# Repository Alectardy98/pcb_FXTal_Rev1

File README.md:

# FXTal Rev. 1 
    A Drop In Replacement PCB For The IBM Model F XT

All Supported Layouts can be seen [HERE](http://www.keyboard-layout-editor.com/#/gists/daab9567d1fe4691fd52719a6adab8b0)

xwhatsit/QMK atmega32u4 pcb for the IBM Model F XT and IBM Bigfoot

This version has been tested and has shown to function properly in both supported layouts.
- The firmware can be found in the firmware folder
- All files for production though JLCPCB can be found in the JLCPCB folder
- This pcb requires an xwhatsit to function, see [purdeaandrei's open source files](https://github.com/purdeaandrei/SMDModelFController)
- Test Points are currently on the pcb, when building make sure to cover the bottom test points with eletrical tape to prevent a short
- The origonal backplate will need to be modified to remove the right PCB mounting peg, to prevent interfearance
- The barrel Plate will need to be modified, a scan of the required holes are provided in folder meta, to help with the task

The PCB thickness should be 0.6mm or 0.08mm. This is thin enough to allow the board to flex into shape.
- 0.8mm tested and working

Standard glossy soldermask is probably the best choice. JLCPCB has had issues with wear on their black soldermask before. They have changed the formula, but a standard green/red/blue/yellow/purple/white/etc. glossy solder mask is probaby the safest bet for keyswitch wear resistance. Higher wear resistance might also be achieved by coating the front of the capacitive pads in silkscreen, as silkscreen is an extra layer of epoxy. I am unsure how this will affect keyfeel or actuation, however.

For connecting the board to an xwhatsit or other controller, I would recommend [3M 8132/06 100](https://www.digikey.com/en/products/detail/3m/8132-06-100/7809902), which has the correct pitch to connect this pcb to an xwhatsit

Capacitive pad footprints have been taken dvjs project the mtf-capacitive Other mesurements have been taken by NeonKight and myself from an origonal IBM F XT. The key matrix of the PCB is custom, made by myself guided by dvjs and purdeaandrei.

Released without warranty, use at your own risk.  
PRs & feedback welcome!

| Authors | 

Alectardy98

| Special Thanks |

djvs - for generial and overall help.   
NeonKnight - for mesurments and reversenginering.   
purdeaandrei - for writing the QMK firmware to work with xwhatsit.

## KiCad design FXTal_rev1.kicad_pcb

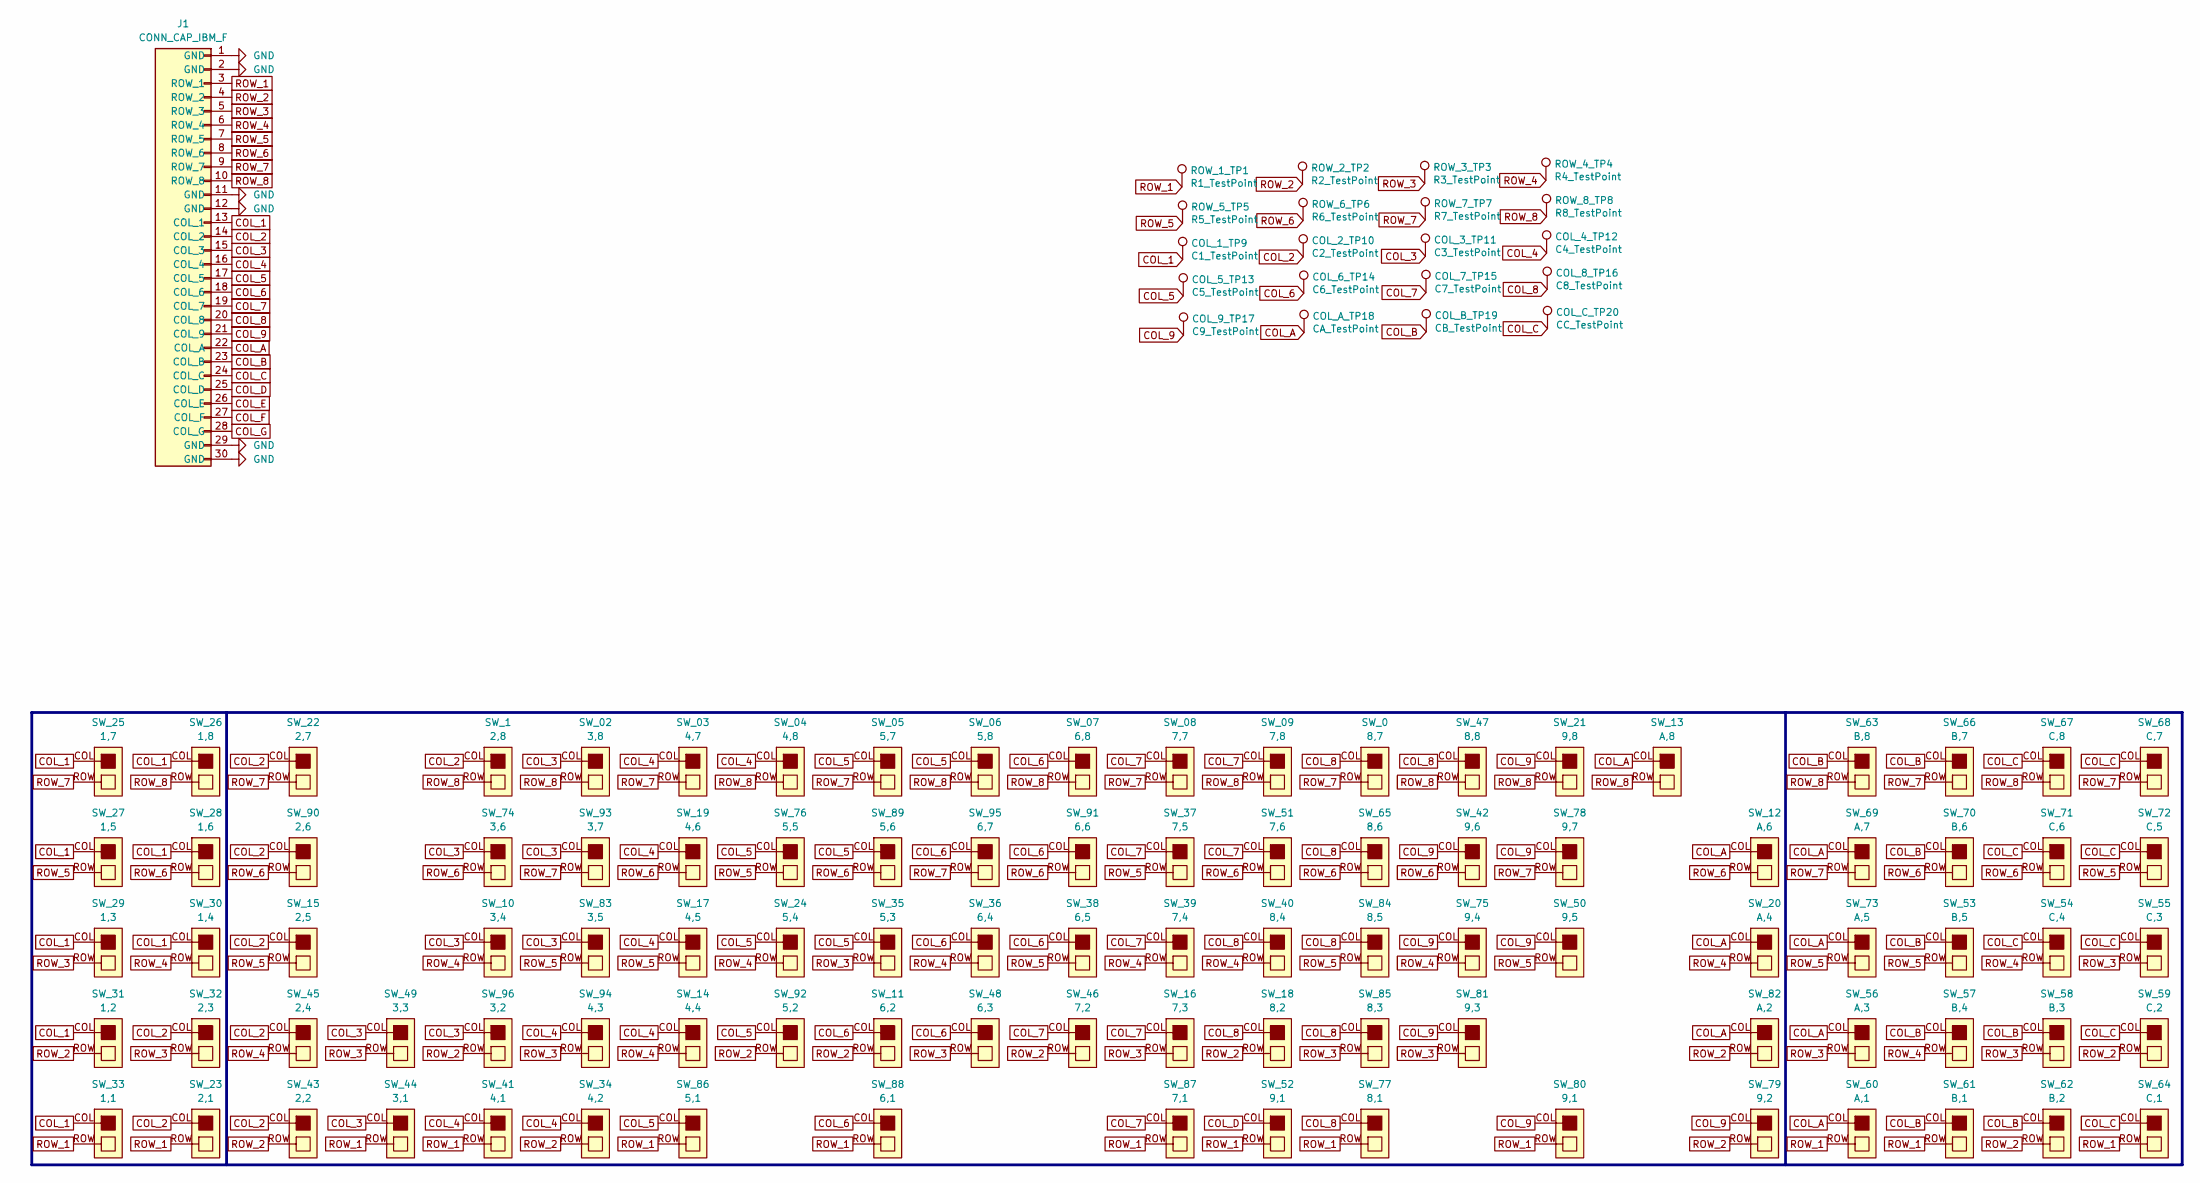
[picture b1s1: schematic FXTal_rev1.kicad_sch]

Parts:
COL_1_TP9: C1_TestPoint; TestPoint_Pad_D1.0mm
COL_2_TP10: C2_TestPoint; TestPoint_Pad_D1.0mm
COL_3_TP11: C3_TestPoint; TestPoint_Pad_D1.0mm
COL_4_TP12: C4_TestPoint; TestPoint_Pad_D1.0mm
COL_5_TP13: C5_TestPoint; TestPoint_Pad_D1.0mm
COL_6_TP14: C6_TestPoint; TestPoint_Pad_D1.0mm
COL_7_TP15: C7_TestPoint; TestPoint_Pad_D1.0mm
COL_8_TP16: C8_TestPoint; TestPoint_Pad_D1.0mm
COL_9_TP17: C9_TestPoint; TestPoint_Pad_D1.0mm
COL_A_TP18: CA_TestPoint; TestPoint_Pad_D1.0mm
COL_B_TP19: CB_TestPoint; TestPoint_Pad_D1.0mm
COL_C_TP20: CC_TestPoint; TestPoint_Pad_D1.0mm
J1: CONN_CAP_IBM_F
ROW_1_TP1: R1_TestPoint; TestPoint_Pad_D1.0mm
ROW_2_TP2: R2_TestPoint; TestPoint_Pad_D1.0mm
ROW_3_TP3: R3_TestPoint; TestPoint_Pad_D1.0mm
ROW_4_TP4: R4_TestPoint; TestPoint_Pad_D1.0mm
ROW_5_TP5: R5_TestPoint; TestPoint_Pad_D1.0mm
ROW_6_TP6: R6_TestPoint; TestPoint_Pad_D1.0mm
ROW_7_TP7: R7_TestPoint; TestPoint_Pad_D1.0mm
ROW_8_TP8: R8_TestPoint; TestPoint_Pad_D1.0mm
SW_0: 8,7; SW_CAP_IBM_F_ALT
SW_1: 2,8; SW_CAP_IBM_F
SW_02: 3,8; SW_CAP_IBM_F_ALT
SW_03: 4,7; SW_CAP_IBM_F
SW_04: 4,8; SW_CAP_IBM_F_ALT
SW_05: 5,7; SW_CAP_IBM_F
SW_06: 5,8; SW_CAP_IBM_F_ALT
SW_07: 6,8; SW_CAP_IBM_F
SW_08: 7,7; SW_CAP_IBM_F_ALT
SW_09: 7,8; SW_CAP_IBM_F
SW_10: 3,4; SW_CAP_IBM_F
SW_11: 6,2; SW_CAP_IBM_F
SW_12: A,6; SW_CAP_IBM_F_ALT
SW_13: A,8; SW_CAP_IBM_F
SW_14: 4,4; SW_CAP_IBM_F_ALT
SW_15: 2,5; SW_CAP_IBM_F
SW_16: 7,3; SW_CAP_IBM_F_ALT
SW_17: 4,5; SW_CAP_IBM_F
SW_18: 8,2; SW_CAP_IBM_F
SW_19: 4,6; SW_CAP_IBM_F
SW_20: A,4; SW_CAP_IBM_F
SW_21: 9,8; SW_CAP_IBM_F_ALT
SW_22: 2,7; SW_CAP_IBM_F_ALT
SW_23: 2,1; SW_CAP_IBM_F
SW_24: 5,4; SW_CAP_IBM_F_ALT
SW_25: 1,7; SW_CAP_IBM_F_ALT
SW_26: 1,8; SW_CAP_IBM_F
SW_27: 1,5; SW_CAP_IBM_F_ALT
SW_28: 1,6; SW_CAP_IBM_F
SW_29: 1,3; SW_CAP_IBM_F_ALT
SW_30: 1,4; SW_CAP_IBM_F
SW_31: 1,2; SW_CAP_IBM_F_ALT
SW_32: 2,3; SW_CAP_IBM_F
SW_33: 1,1; SW_CAP_IBM_F_ALT
SW_34: 4,2; SW_CAP_IBM_F
SW_35: 5,3; SW_CAP_IBM_F
SW_36: 6,4; SW_CAP_IBM_F_ALT
SW_37: 7,5; SW_CAP_IBM_F
SW_38: 6,5; SW_CAP_IBM_F
SW_39: 7,4; SW_CAP_IBM_F_ALT
SW_40: 8,4; SW_CAP_IBM_F
SW_41: 4,1; SW_CAP_IBM_F_ALT
SW_42: 9,6; SW_CAP_IBM_F
SW_43: 2,2; SW_CAP_IBM_F
SW_44: 3,1; SW_CAP_IBM_F_ALT
SW_45: 2,4; SW_CAP_IBM_F
SW_46: 7,2; SW_CAP_IBM_F_ALT
SW_47: 8,8; SW_CAP_IBM_F
SW_48: 6,3; SW_CAP_IBM_F_ALT
SW_49: 3,3; SW_CAP_IBM_F_ALT
SW_50: 9,5; SW_CAP_IBM_F_ALT
SW_51: 7,6; SW_CAP_IBM_F_ALT
SW_52: 9,1; CAL_CAP_IBM_F
SW_53: B,5; SW_CAP_IBM_F
SW_54: C,4; SW_CAP_IBM_F_ALT
SW_55: C,3; SW_CAP_IBM_F
SW_56: A,3; SW_CAP_IBM_F_ALT
SW_57: B,4; SW_CAP_IBM_F
SW_58: B,3; SW_CAP_IBM_F
SW_59: C,2; SW_CAP_IBM_F_ALT
SW_60: A,1; SW_CAP_IBM_F_ALT
SW_61: B,1; SW_CAP_IBM_F
SW_62: B,2; SW_CAP_IBM_F_ALT
SW_63: B,8; SW_CAP_IBM_F
SW_64: C,1; SW_CAP_IBM_F
SW_65: 8,6; SW_CAP_IBM_F
SW_66: B,7; SW_CAP_IBM_F_ALT
SW_67: C,8; SW_CAP_IBM_F
SW_68: C,7; SW_CAP_IBM_F_ALT
SW_69: A,7; SW_CAP_IBM_F_ALT
SW_70: B,6; SW_CAP_IBM_F
SW_71: C,6; SW_CAP_IBM_F
SW_72: C,5; SW_CAP_IBM_F_ALT
SW_73: A,5; SW_CAP_IBM_F_ALT
SW_74: 3,6; SW_CAP_IBM_F_ALT
SW_75: 9,4; SW_CAP_IBM_F
SW_76: 5,5; SW_CAP_IBM_F
SW_77: 8,1; SW_CAP_IBM_F_ALT
SW_78: 9,7; SW_CAP_IBM_F
SW_79: 9,2; SW_CAP_IBM_F_ALT
SW_80: 9,1; SW_CAP_IBM_F_ALT
SW_81: 9,3; SW_CAP_IBM_F
SW_82: A,2; SW_CAP_IBM_F
SW_83: 3,5; SW_CAP_IBM_F_ALT
SW_84: 8,5; SW_CAP_IBM_F_ALT
SW_85: 8,3; SW_CAP_IBM_F_ALT
SW_86: 5,1; SW_CAP_IBM_F
SW_87: 7,1; SW_CAP_IBM_F_ALT
SW_88: 6,1; SW_CAP_IBM_F_ALT
SW_89: 5,6; SW_CAP_IBM_F_ALT
SW_90: 2,6; SW_CAP_IBM_F_ALT
SW_91: 6,6; SW_CAP_IBM_F
SW_92: 5,2; SW_CAP_IBM_F_ALT
SW_93: 3,7; SW_CAP_IBM_F_ALT
SW_94: 4,3; SW_CAP_IBM_F
SW_95: 6,7; SW_CAP_IBM_F_ALT
SW_96: 3,2; SW_CAP_IBM_F

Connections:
COL_1: COL_1_TP9.1, J1.13 (COL_1), SW_25.COL, SW_26.COL, SW_27.COL, SW_28.COL, SW_29.COL, SW_30.COL, SW_31.COL, SW_33.COL
COL_2: COL_2_TP10.1, J1.14 (COL_2), SW_1.COL, SW_15.COL, SW_22.COL, SW_23.COL, SW_32.COL, SW_43.COL, SW_45.COL, SW_90.COL
COL_3: COL_3_TP11.1, J1.15 (COL_3), SW_02.COL, SW_10.COL, SW_44.COL, SW_49.COL, SW_74.COL, SW_83.COL, SW_93.COL, SW_96.COL
COL_4: COL_4_TP12.1, J1.16 (COL_4), SW_03.COL, SW_04.COL, SW_14.COL, SW_17.COL, SW_19.COL, SW_34.COL, SW_41.COL, SW_94.COL
COL_5: COL_5_TP13.1, J1.17 (COL_5), SW_05.COL, SW_06.COL, SW_24.COL, SW_35.COL, SW_76.COL, SW_86.COL, SW_89.COL, SW_92.COL
COL_6: COL_6_TP14.1, J1.18 (COL_6), SW_07.COL, SW_11.COL, SW_36.COL, SW_38.COL, SW_48.COL, SW_88.COL, SW_91.COL, SW_95.COL
COL_7: COL_7_TP15.1, J1.19 (COL_7), SW_08.COL, SW_09.COL, SW_16.COL, SW_37.COL, SW_39.COL, SW_46.COL, SW_51.COL, SW_87.COL
COL_8: COL_8_TP16.1, J1.20 (COL_8), SW_0.COL, SW_18.COL, SW_40.COL, SW_47.COL, SW_65.COL, SW_77.COL, SW_84.COL, SW_85.COL
COL_9: COL_9_TP17.1, J1.21 (COL_9), SW_21.COL, SW_42.COL, SW_50.COL, SW_75.COL, SW_78.COL, SW_79.COL, SW_80.COL, SW_81.COL
COL_A: COL_A_TP18.1, J1.22 (COL_A), SW_12.COL, SW_13.COL, SW_20.COL, SW_56.COL, SW_60.COL, SW_69.COL, SW_73.COL, SW_82.COL
COL_B: COL_B_TP19.1, J1.23 (COL_B), SW_53.COL, SW_57.COL, SW_58.COL, SW_61.COL, SW_62.COL, SW_63.COL, SW_66.COL, SW_70.COL
COL_C: COL_C_TP20.1, J1.24 (COL_C), SW_54.COL, SW_55.COL, SW_59.COL, SW_64.COL, SW_67.COL, SW_68.COL, SW_71.COL, SW_72.COL
COL_D: J1.25 (COL_D), SW_52.COL
COL_E: J1.26 (COL_E)
COL_F: J1.27 (COL_F)
COL_G: J1.28 (COL_G)
GND: J1.1 (GND), J1.2 (GND), J1.11 (GND), J1.12 (GND), J1.29 (GND), J1.30 (GND)
ROW_1: J1.3 (ROW_1), ROW_1_TP1.1, SW_23.ROW, SW_33.ROW, SW_41.ROW, SW_44.ROW, SW_52.ROW, SW_60.ROW, SW_61.ROW, SW_64.ROW, SW_77.ROW, SW_80.ROW, SW_86.ROW, SW_87.ROW, SW_88.ROW
ROW_2: J1.4 (ROW_2), ROW_2_TP2.1, SW_11.ROW, SW_18.ROW, SW_31.ROW, SW_34.ROW, SW_43.ROW, SW_46.ROW, SW_59.ROW, SW_62.ROW, SW_79.ROW, SW_82.ROW, SW_92.ROW, SW_96.ROW
ROW_3: J1.5 (ROW_3), ROW_3_TP3.1, SW_16.ROW, SW_29.ROW, SW_32.ROW, SW_35.ROW, SW_48.ROW, SW_49.ROW, SW_55.ROW, SW_56.ROW, SW_58.ROW, SW_81.ROW, SW_85.ROW, SW_94.ROW
ROW_4: J1.6 (ROW_4), ROW_4_TP4.1, SW_10.ROW, SW_14.ROW, SW_20.ROW, SW_24.ROW, SW_30.ROW, SW_36.ROW, SW_39.ROW, SW_40.ROW, SW_45.ROW, SW_54.ROW, SW_57.ROW, SW_75.ROW
ROW_5: J1.7 (ROW_5), ROW_5_TP5.1, SW_15.ROW, SW_17.ROW, SW_27.ROW, SW_37.ROW, SW_38.ROW, SW_50.ROW, SW_53.ROW, SW_72.ROW, SW_73.ROW, SW_76.ROW, SW_83.ROW, SW_84.ROW
ROW_6: J1.8 (ROW_6), ROW_6_TP6.1, SW_12.ROW, SW_19.ROW, SW_28.ROW, SW_42.ROW, SW_51.ROW, SW_65.ROW, SW_70.ROW, SW_71.ROW, SW_74.ROW, SW_89.ROW, SW_90.ROW, SW_91.ROW
ROW_7: J1.9 (ROW_7), ROW_7_TP7.1, SW_0.ROW, SW_03.ROW, SW_05.ROW, SW_08.ROW, SW_22.ROW, SW_25.ROW, SW_66.ROW, SW_68.ROW, SW_69.ROW, SW_78.ROW, SW_93.ROW, SW_95.ROW
ROW_8: J1.10 (ROW_8), ROW_8_TP8.1, SW_1.ROW, SW_02.ROW, SW_04.ROW, SW_06.ROW, SW_07.ROW, SW_09.ROW, SW_13.ROW, SW_21.ROW, SW_26.ROW, SW_47.ROW, SW_63.ROW, SW_67.ROW

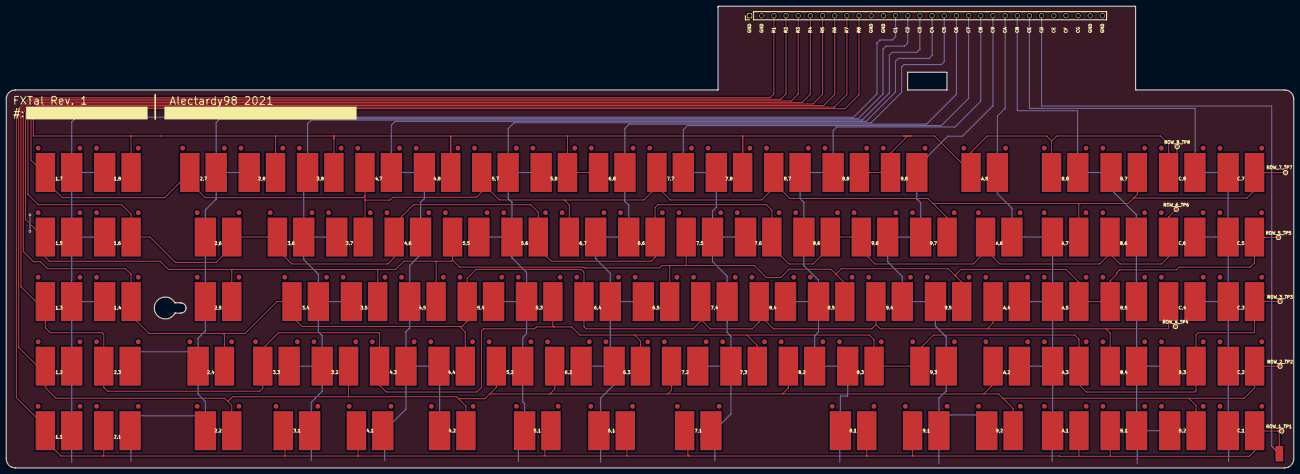
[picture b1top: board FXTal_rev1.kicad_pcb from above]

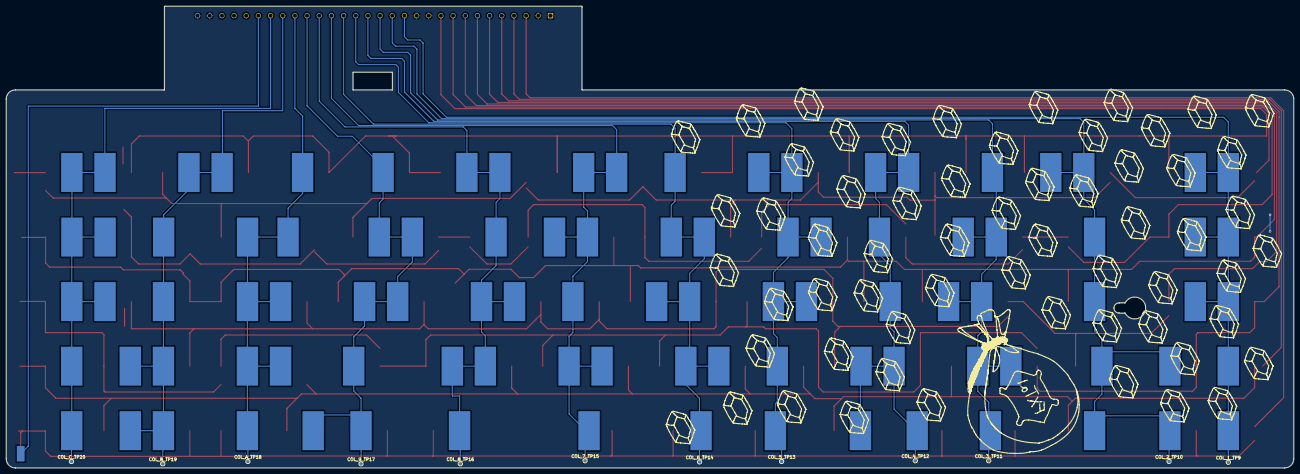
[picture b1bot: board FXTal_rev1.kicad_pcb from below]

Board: 2 copper layers, 419.0 x 150.2 mm, 118 parts (12 on the bottom side), 22 nets.

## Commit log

2021-10-29 Push
2021-12-13 firmware add
2022-01-03 name change to rev 1
2022-01-03 changes to wireing
2022-01-03 push fix rev 1
2022-07-18 Git Update Push
2022-07-18 Github Fix Push
2023-07-04 clean up
